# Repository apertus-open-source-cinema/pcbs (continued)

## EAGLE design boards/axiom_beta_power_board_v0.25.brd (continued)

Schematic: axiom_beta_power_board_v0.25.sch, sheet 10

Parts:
C49, C52, C55, C58, C61: 4u7; 0603-B
C50, C53, C56, C59, C62: DNP; 0402-B
C51, C54, C57, C60, C63: 10u; 0603-B
L9, L10, L11, L12, L13: L0805-A; 0805-A
MCN: MCP1727-ADJE/MF; DFN65P300X300X100-9N
MCS: MCP1727-ADJE/MF; DFN65P300X300X100-9N
MXN: MCP1727-ADJE/MF; DFN65P300X300X100-9N
MXS: MCP1727-ADJE/MF; DFN65P300X300X100-9N
R33, R35, R39, R41: RD; 0402-B
R34, R36, R40, R42: RC; 0402-B
R37: 102k; 0402-B
R38: 20k; 0402-B
R67, R68, R69, R70, R71, R72: R1206-B; 1206-B
R81: 2k0; 0402-B
R82: 1k6; 0402-B
R83: 2k7; 0402-B
R90: 15k; 0402-B
R91: 1k; 0402-B
U7: MCP23018-E/MJ; QFN50P400X400X80-25N
U14, U15, U22: PAC1720; DFN3X3_10LEAD
VIO: MCP1727-ADJE/MF; DFN65P300X300X100-9N

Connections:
BETA_5V: R70.1, U22.3 (SENSE2+); also elsewhere on the board
BETA_5V': C51.1, C54.1, C57.1, C60.1, C63.1, MCN.1 (VIN), MCN.2 (VIN), MCS.1 (VIN), MCS.2 (VIN), MXN.1 (VIN), MXN.2 (VIN), MXS.1 (VIN), MXS.2 (VIN), R70.2, U22.4 (SENSE2-), VIO.1 (VIN), VIO.2 (VIN); also elsewhere on the board
CSO_NE_V: R67.2, U14.2 (SENSE1-); also elsewhere on the board
CSO_N_V': L12.2, R67.1, U14.1 (SENSE1+)
CSO_SW_V: R71.2, U15.2 (SENSE1-); also elsewhere on the board
CSO_S_V': L10.2, R71.1, U15.1 (SENSE1+)
GND: C49.2, C50.2, C51.2, C52.2, C53.2, C54.2, C55.2, C56.2, C57.2, C58.2, C59.2, C60.2, C61.2, C62.2, C63.2, MCN.4 (GND), MCN.9 (EP), MCS.4 (GND), MCS.9 (EP), MXN.4 (GND), MXN.9 (EP), MXS.4 (GND), MXS.9 (EP), R34.2, R36.2, R38.2, R40.2, R42.2, R81.2, R82.2, R83.2, R91.2, U7.23 (VSS), U7.25 (VSS), U14.5 (GND), U14.EPAD (GND), U15.5 (GND), U15.EPAD (GND), U22.5 (GND), U22.EPAD (GND), VIO.4 (GND), VIO.9 (EP); also elsewhere on the board
MCN_EN: MCN.3 (!SHDN), U7.18 (GPA3)
MCN_PG: MCN.5 (PWRGD), U7.17 (GPA2)
MCS_EN: MCS.3 (!SHDN), U7.22 (GPA7)
MCS_PG: MCS.5 (PWRGD), U7.21 (GPA6)
MXN_EN: MXN.3 (!SHDN), U7.16 (GPA1)
MXN_PG: MXN.5 (PWRGD), U7.15 (GPA0)
MXS_EN: MXS.3 (!SHDN), U7.1 (GPB1)
MXS_PG: MXS.5 (PWRGD), U7.24 (GPB0)
unnamed: C49.1, L9.1, MXS.8 (VOUT), R41.1
unnamed: MXS.7 (ADJ), R41.2, R42.1
unnamed: C50.1, MXS.6 (CDELAY)
unnamed: R81.1, U14.6 (ASEL)
unnamed: R83.1, U15.6 (ASEL)
unnamed: C52.1, L10.1, MCS.8 (VOUT), R39.1
unnamed: MCS.7 (ADJ), R39.2, R40.1
unnamed: C53.1, MCS.6 (CDELAY)
unnamed: R82.1, U22.6 (ASEL)
unnamed: C55.1, L11.1, R37.1, VIO.8 (VOUT)
unnamed: R37.2, R38.1, VIO.7 (ADJ)
unnamed: C56.1, VIO.6 (CDELAY)
unnamed: C58.1, L12.1, MCN.8 (VOUT), R35.1
unnamed: MCN.7 (ADJ), R35.2, R36.1
unnamed: C59.1, MCN.6 (CDELAY)
unnamed: C61.1, L13.1, MXN.8 (VOUT), R33.1
unnamed: MXN.7 (ADJ), R33.2, R34.1
unnamed: C62.1, MXN.6 (CDELAY)
unnamed: R90.2, R91.1, U7.11 (ADDR)
PCIE_N_V: R68.2, U14.4 (SENSE2-); also elsewhere on the board
PCIE_N_V': L13.2, R68.1, U14.3 (SENSE2+)
PCIE_S_V: R72.2, U15.4 (SENSE2-); also elsewhere on the board
PCIE_S_V': L9.2, R72.1, U15.3 (SENSE2+)
PMOD_SCL: U7.9 (SCL), U14.9 (SMCLK), U15.9 (SMCLK), U22.9 (SMCLK); also elsewhere on the board
PMOD_SDA: U7.10 (SDA), U14.8 (SMDATA), U15.8 (SMDATA), U22.8 (SMDATA); also elsewhere on the board
VCC: R90.1, U7.8 (VDD), U7.12 (!RESET), U14.10 (VDD), U15.10 (VDD), U22.10 (VDD); also elsewhere on the board
VCCIO: L11.2; also elsewhere on the board
VIO_EN: U7.20 (GPA5), VIO.3 (!SHDN)
VIO_PG: U7.19 (GPA4), VIO.5 (PWRGD)
ZED_5V: R69.1, U22.1 (SENSE1+); also elsewhere on the board
ZED_5V': R69.2, U22.2 (SENSE1-); also elsewhere on the board

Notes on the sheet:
AXIOM Beta Test
Copyright (C) 2015 H.Poetzl Licensed under CERN OHL v.1.2
Power, Control and Sensing
[ID=0x20]
[0x29]
[0x28]
[0x2A]

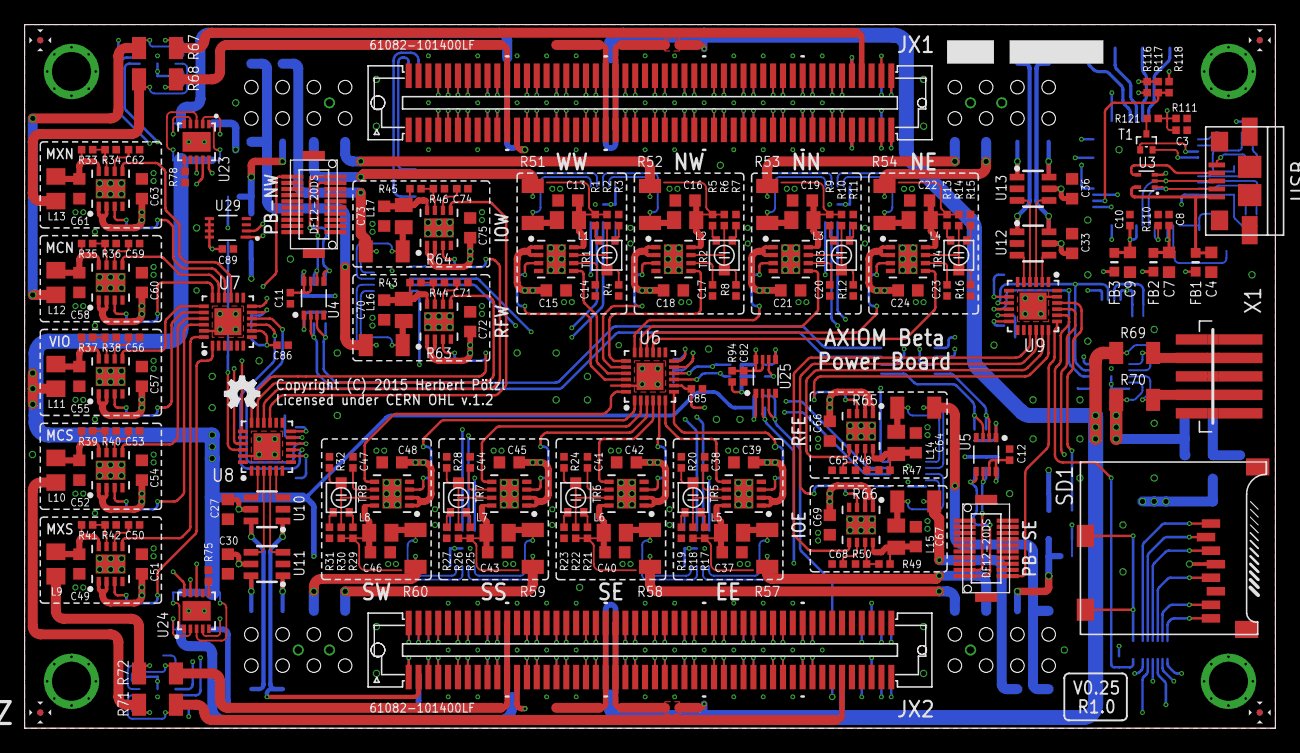
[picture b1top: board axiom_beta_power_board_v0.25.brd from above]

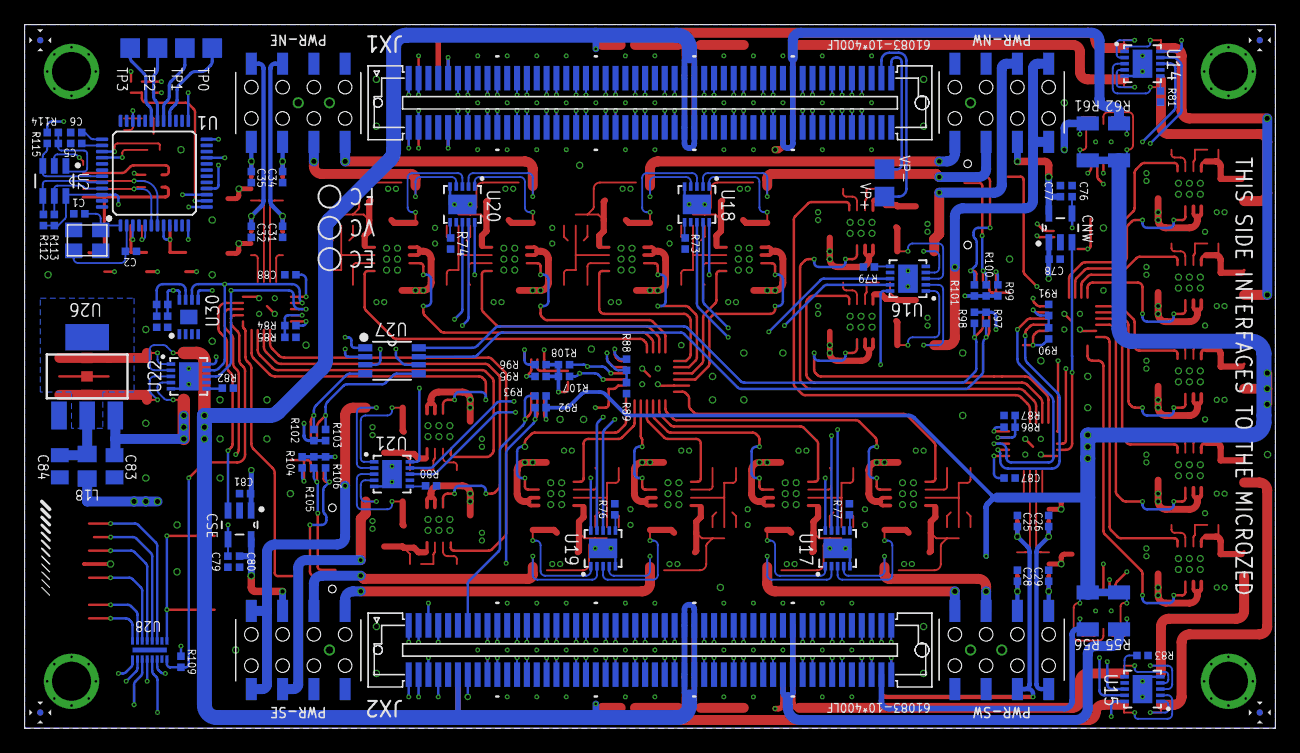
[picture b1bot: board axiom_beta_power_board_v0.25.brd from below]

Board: 4 copper layers, 101.6 x 57.1 mm, 309 parts (97 on the bottom side), 366 nets.

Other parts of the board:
LOGO1: OSHW_LOGO_FILLX0100-NT; OSHW_FILLX100_NOTEXT

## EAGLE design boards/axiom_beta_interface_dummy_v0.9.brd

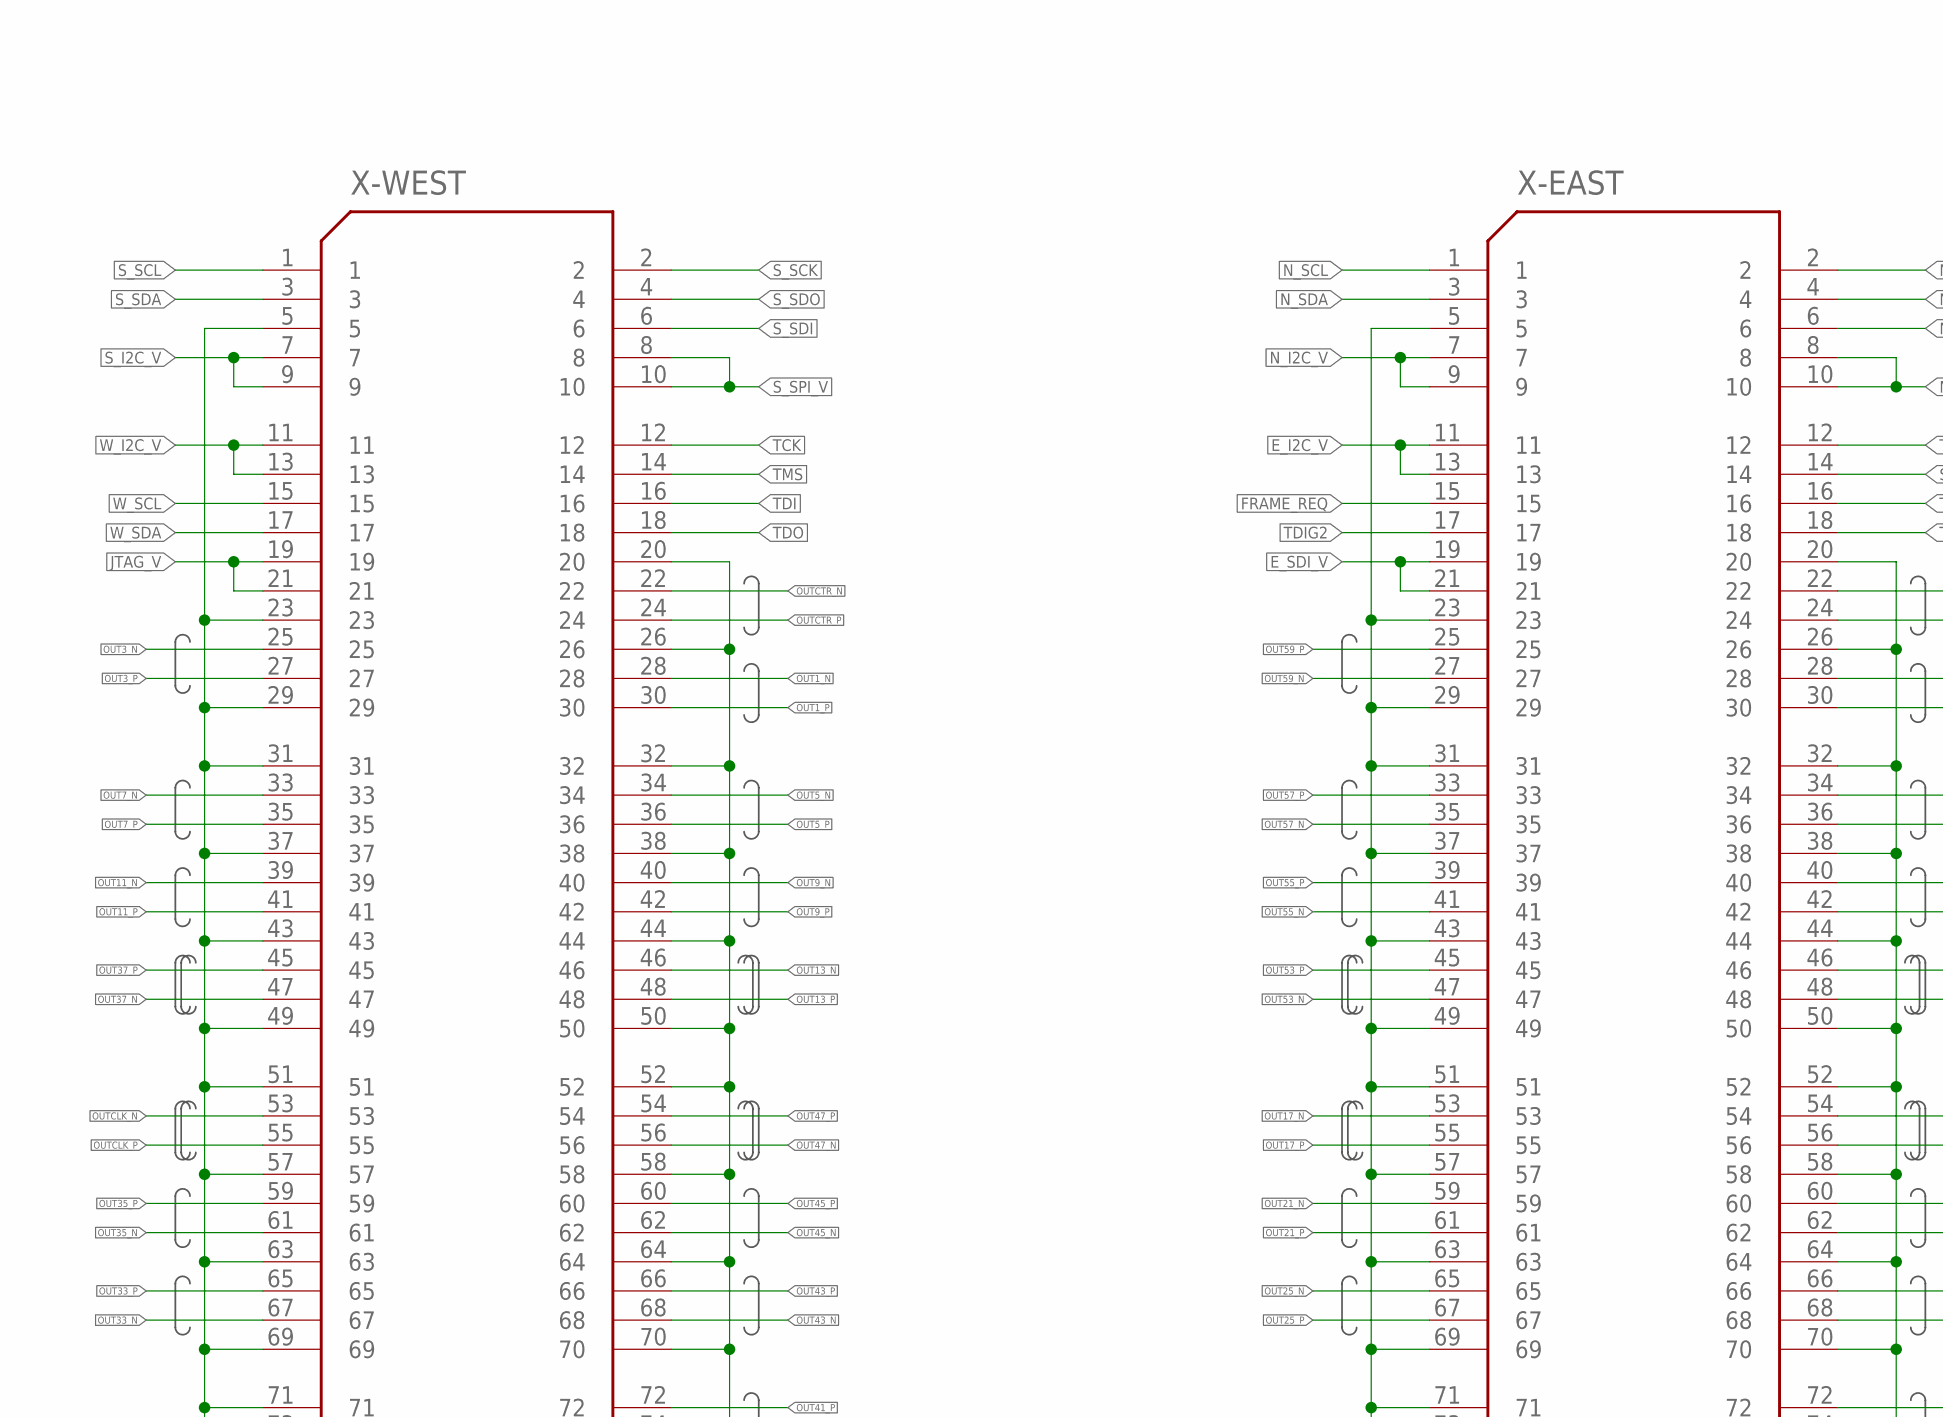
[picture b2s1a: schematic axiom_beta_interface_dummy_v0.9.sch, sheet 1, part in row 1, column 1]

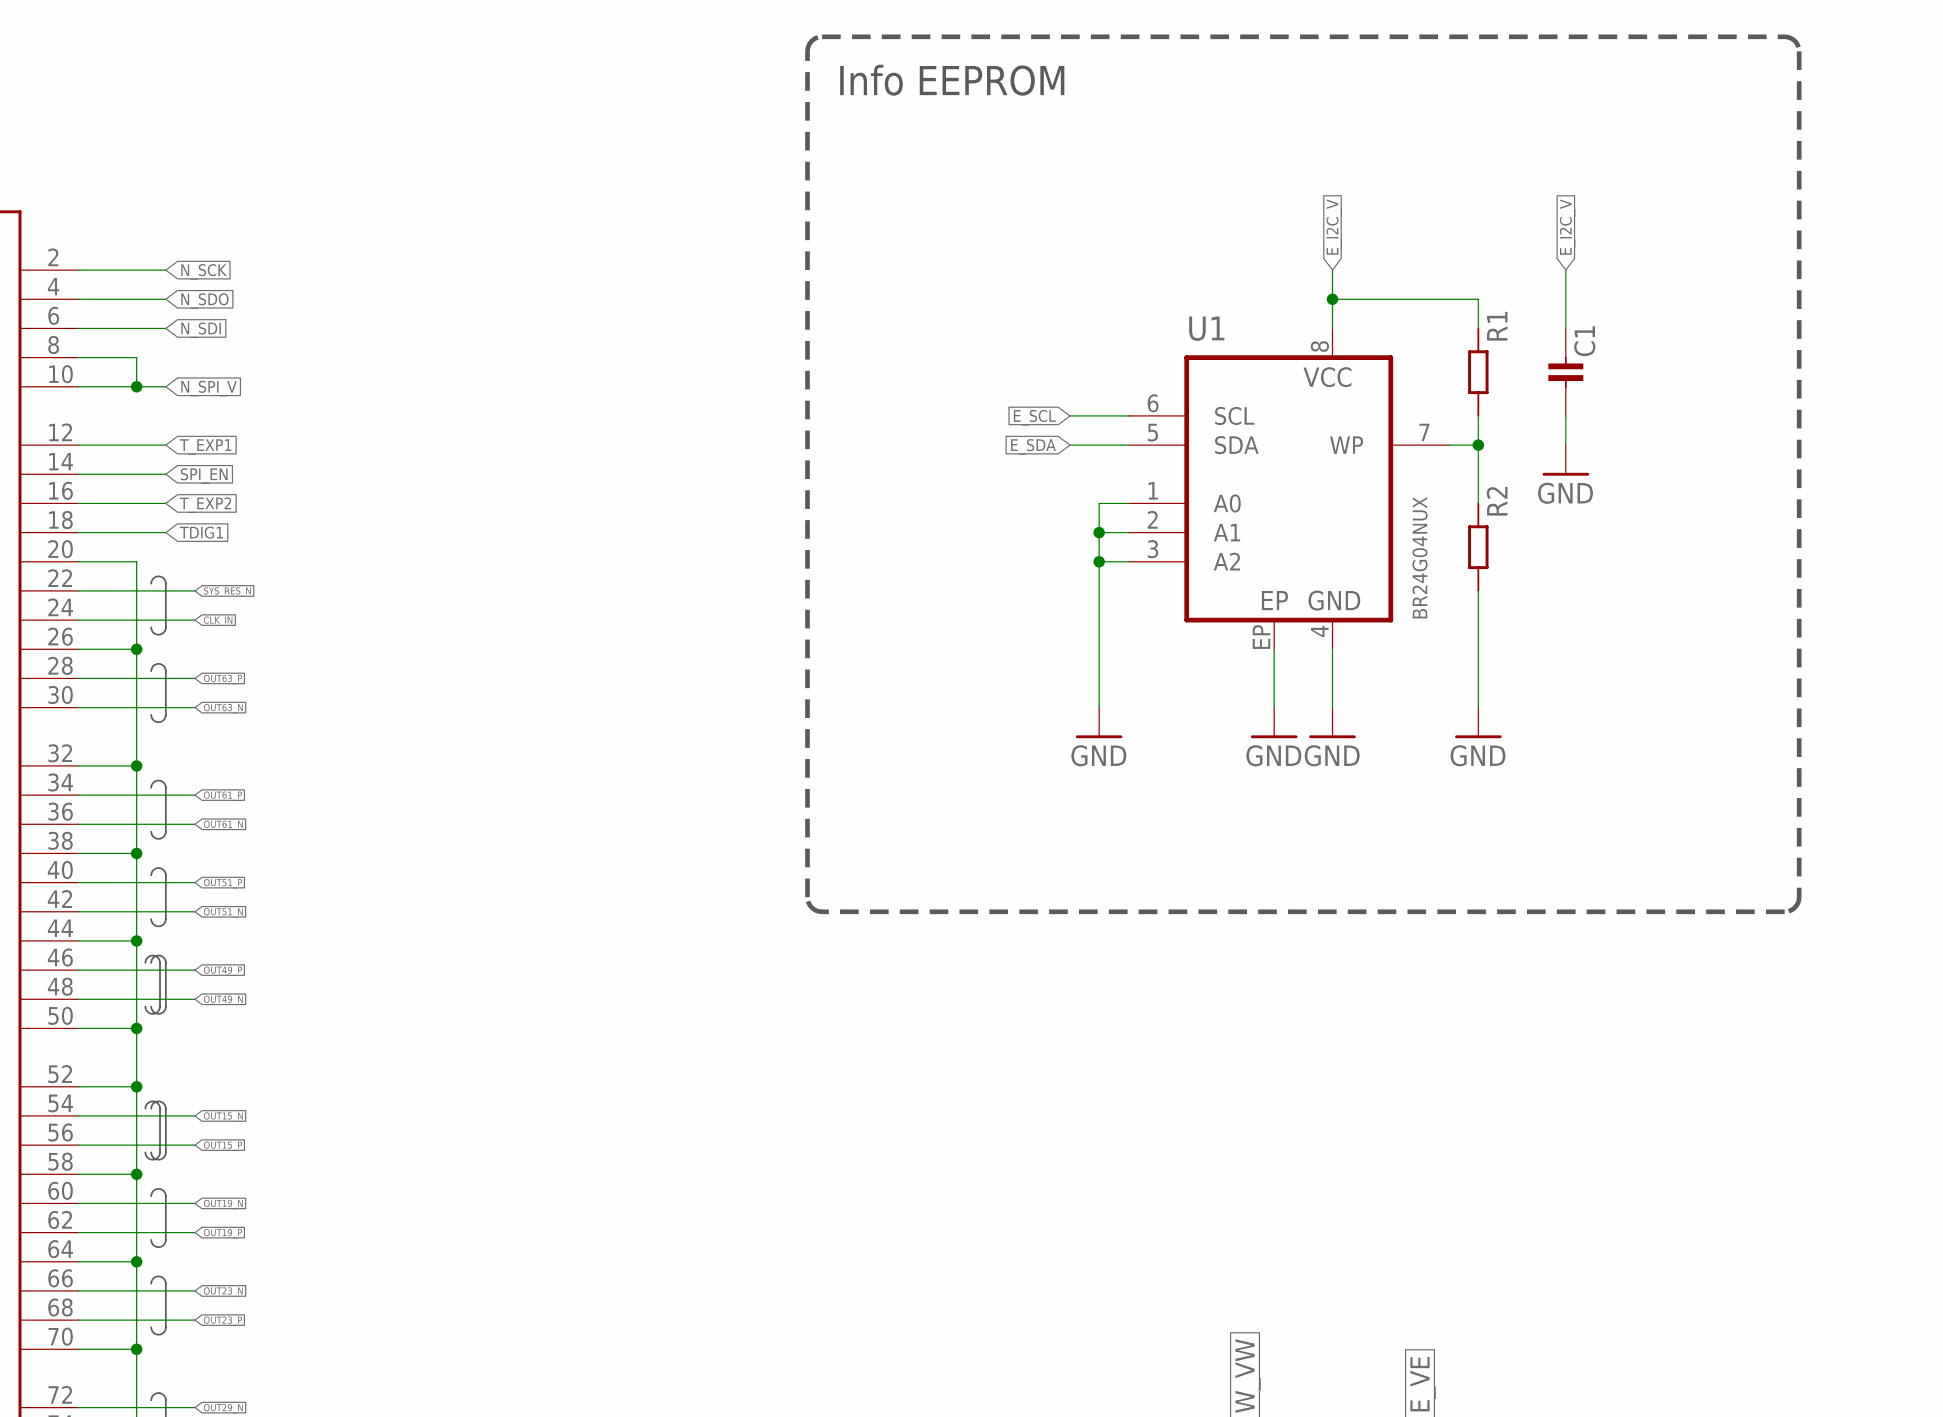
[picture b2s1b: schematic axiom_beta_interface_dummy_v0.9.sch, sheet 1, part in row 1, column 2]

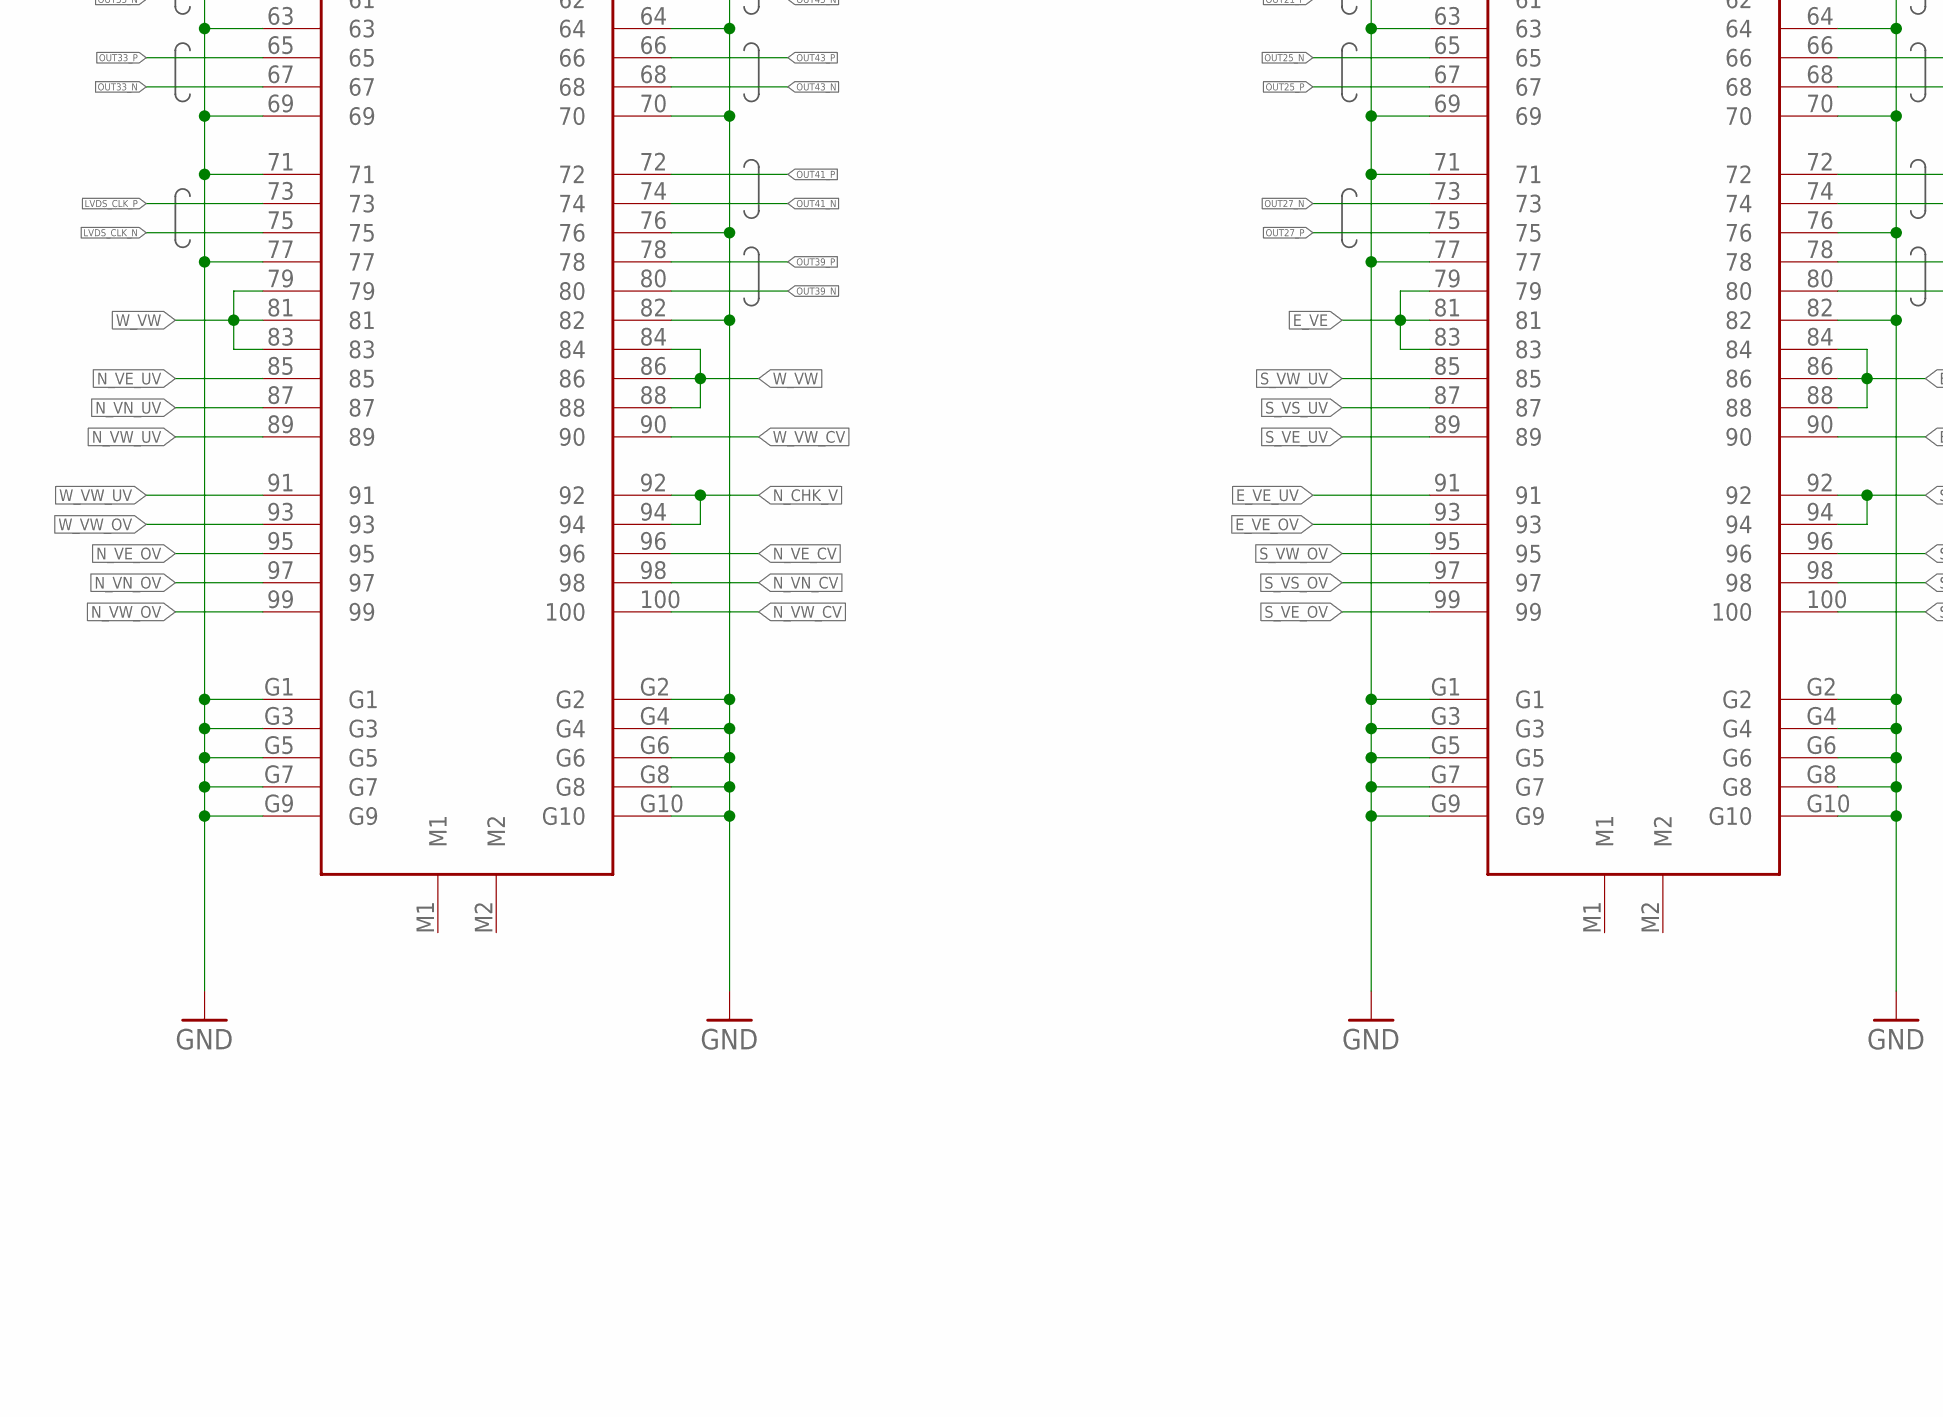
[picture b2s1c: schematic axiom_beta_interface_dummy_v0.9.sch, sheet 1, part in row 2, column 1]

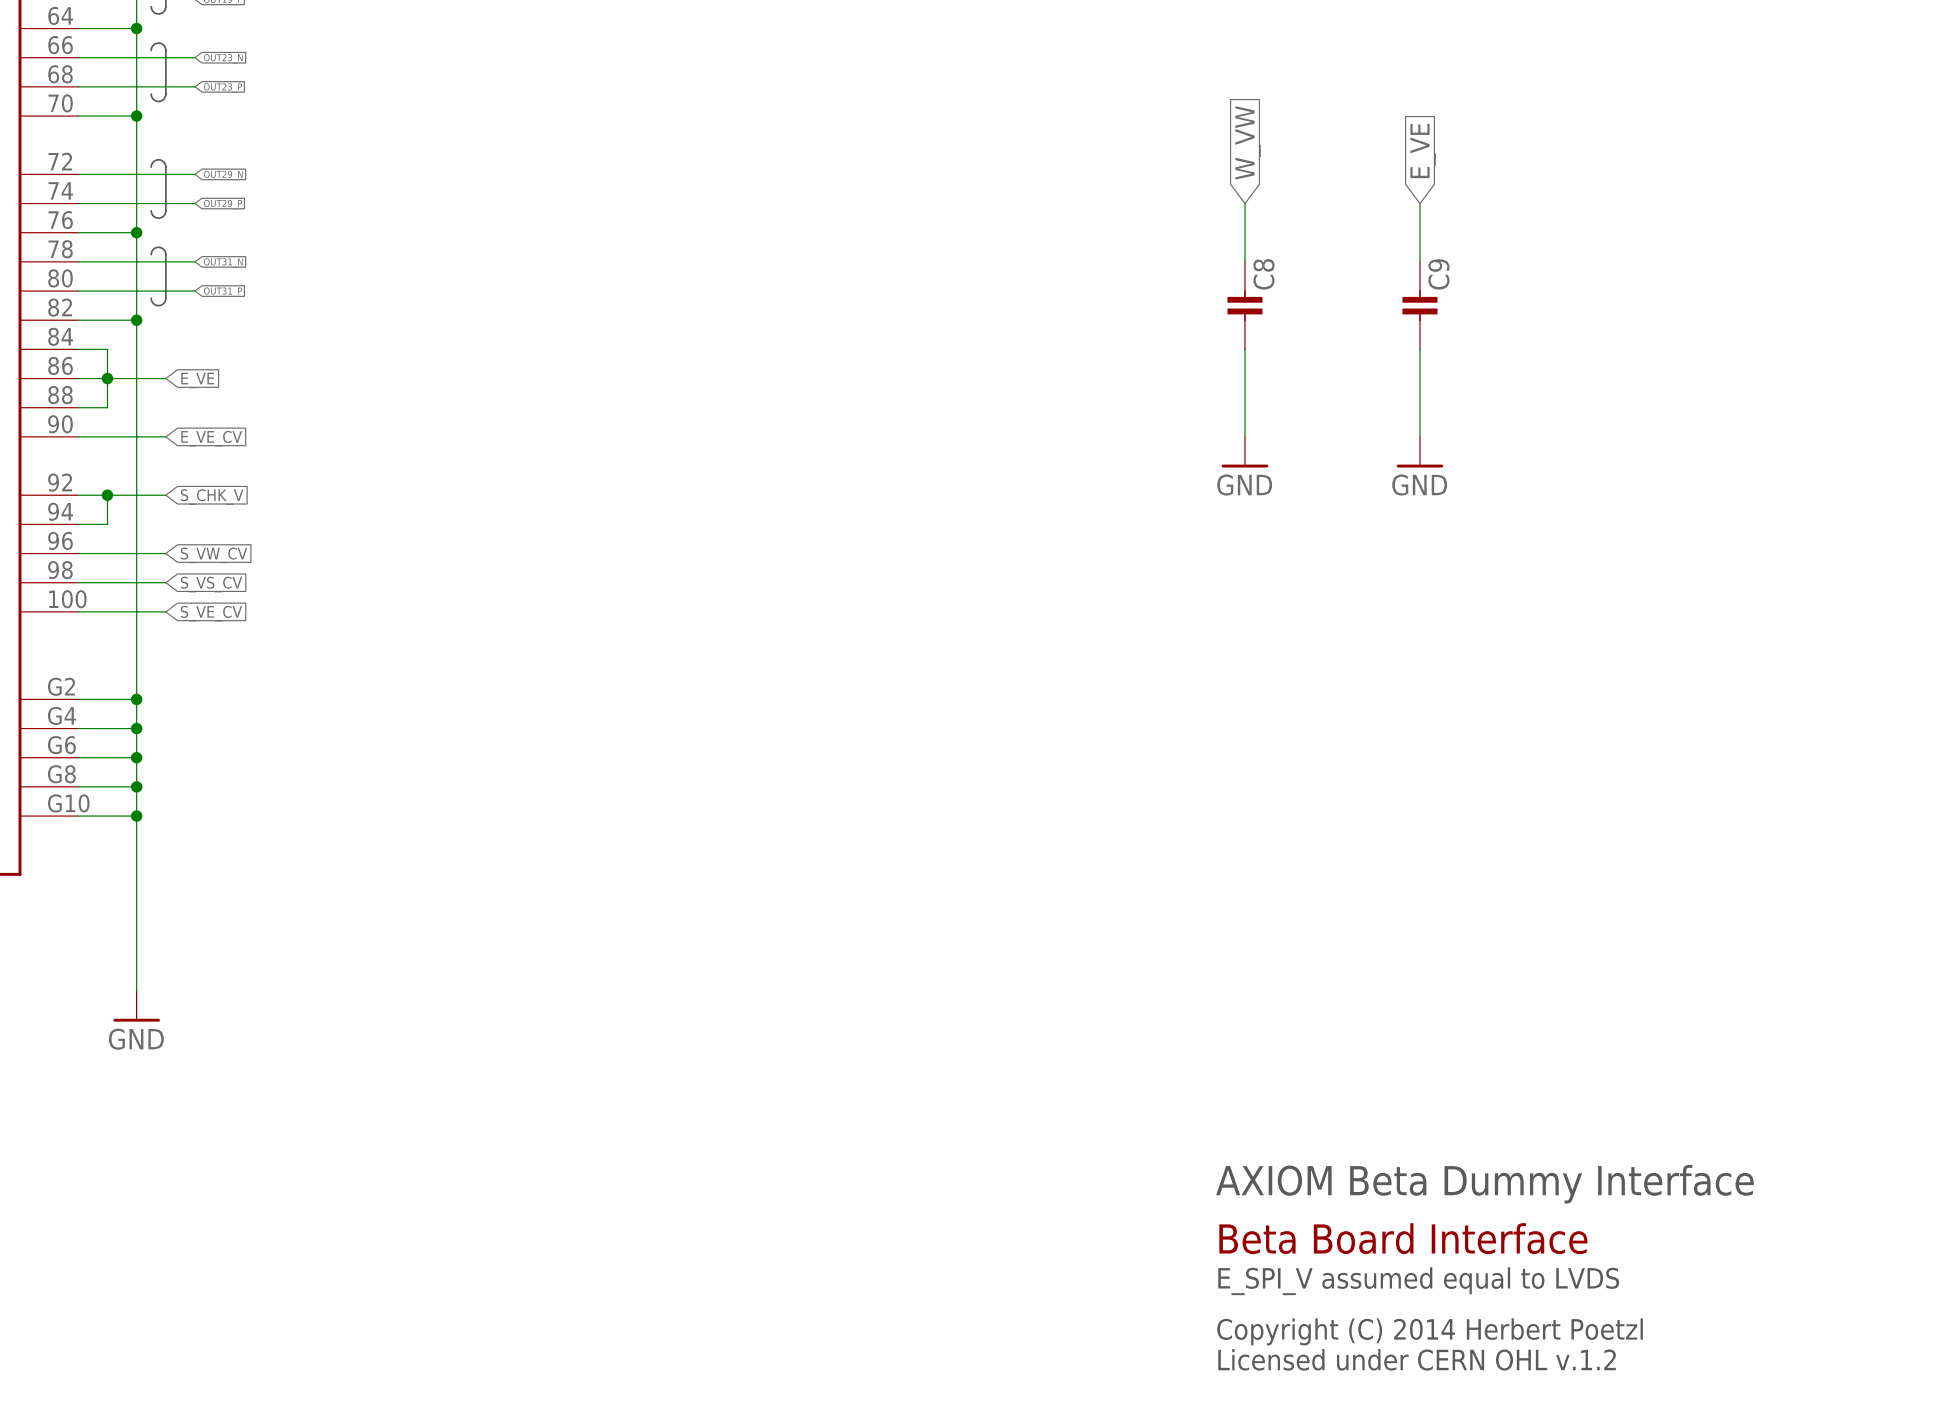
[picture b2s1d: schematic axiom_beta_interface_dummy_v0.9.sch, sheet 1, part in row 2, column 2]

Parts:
C1: C0402-B; 0402-B
C8, C9: C0805-B; 0805-B
R1, R2: R0402-B; 0402-B
U1: BR24G04NUX; DFN200X300X100-9N
X-EAST: FX10-100/10P; FX10A-100P/10
X-WEST: FX10-100/10P; FX10A-100P/10

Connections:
CLK_IN: X-EAST.24; also elsewhere on the board
E_I2C_V: C1.1, R1.1, U1.8 (VCC), X-EAST.11, X-EAST.13
E_SCL: U1.6 (SCL)
E_SDA: U1.5 (SDA)
E_SDI_V: X-EAST.19, X-EAST.21
E_VE: C9.1, X-EAST.79, X-EAST.81, X-EAST.83, X-EAST.84, X-EAST.86, X-EAST.88; also elsewhere on the board
E_VE_CV: X-EAST.90
E_VE_OV: X-EAST.93
E_VE_UV: X-EAST.91
FRAME_REQ: X-EAST.15; also elsewhere on the board
GND: C1.2, C8.2, C9.2, R2.2, U1.1 (A0), U1.2 (A1), U1.3 (A2), U1.4 (GND), U1.EP, X-EAST.5, X-EAST.20, X-EAST.23, X-EAST.26, X-EAST.29, X-EAST.31, X-EAST.32, X-EAST.37, X-EAST.38, X-EAST.43, X-EAST.44, X-EAST.49, X-EAST.50, X-EAST.51, X-EAST.52, X-EAST.57, X-EAST.58, X-EAST.63, X-EAST.64, X-EAST.69, X-EAST.70, X-EAST.71, X-EAST.76, X-EAST.77, X-EAST.82, X-EAST.G1, X-EAST.G2, X-EAST.G3, X-EAST.G4, X-EAST.G5, X-EAST.G6, X-EAST.G7, X-EAST.G8, X-EAST.G9, X-EAST.G10, X-WEST.5, X-WEST.20, X-WEST.23, X-WEST.26, X-WEST.29, X-WEST.31, X-WEST.32, X-WEST.37, X-WEST.38, X-WEST.43, X-WEST.44, X-WEST.49, X-WEST.50, X-WEST.51, X-WEST.52, X-WEST.57, X-WEST.58, X-WEST.63, X-WEST.64, X-WEST.69, X-WEST.70, X-WEST.71, X-WEST.76, X-WEST.77, X-WEST.82, X-WEST.G1, X-WEST.G2, X-WEST.G3, X-WEST.G4, X-WEST.G5, X-WEST.G6, X-WEST.G7, X-WEST.G8, X-WEST.G9, X-WEST.G10; also elsewhere on the board
JTAG_V: X-WEST.19, X-WEST.21
LVDS_CLK_N: X-WEST.75; also elsewhere on the board
LVDS_CLK_P: X-WEST.73; also elsewhere on the board
unnamed: R1.2, R2.1, U1.7 (WP)
N_CHK_V: X-WEST.92, X-WEST.94; also elsewhere on the board
N_I2C_V: X-EAST.7, X-EAST.9; also elsewhere on the board
N_SCK: X-EAST.2; also elsewhere on the board
N_SCL: X-EAST.1; also elsewhere on the board
N_SDA: X-EAST.3; also elsewhere on the board
N_SDI: X-EAST.6; also elsewhere on the board
N_SDO: X-EAST.4; also elsewhere on the board
N_SPI_V: X-EAST.8, X-EAST.10; also elsewhere on the board
N_VE_CV: X-WEST.96; also elsewhere on the board
N_VE_OV: X-WEST.95; also elsewhere on the board
N_VE_UV: X-WEST.85; also elsewhere on the board
N_VN_CV: X-WEST.98; also elsewhere on the board
N_VN_OV: X-WEST.97; also elsewhere on the board
N_VN_UV: X-WEST.87; also elsewhere on the board
N_VW_CV: X-WEST.100; also elsewhere on the board
N_VW_OV: X-WEST.99; also elsewhere on the board
N_VW_UV: X-WEST.89; also elsewhere on the board
OUT1_N: X-WEST.28; also elsewhere on the board
OUT1_P: X-WEST.30; also elsewhere on the board
OUT3_N: X-WEST.25; also elsewhere on the board
OUT3_P: X-WEST.27; also elsewhere on the board
OUT5_N: X-WEST.34; also elsewhere on the board
OUT5_P: X-WEST.36; also elsewhere on the board
OUT7_N: X-WEST.33; also elsewhere on the board
OUT7_P: X-WEST.35; also elsewhere on the board
OUT9_N: X-WEST.40; also elsewhere on the board
OUT9_P: X-WEST.42; also elsewhere on the board
OUT11_N: X-WEST.39; also elsewhere on the board
OUT11_P: X-WEST.41; also elsewhere on the board
OUT13_N: X-WEST.46; also elsewhere on the board
OUT13_P: X-WEST.48; also elsewhere on the board
OUT15_N: X-EAST.54; also elsewhere on the board
OUT15_P: X-EAST.56; also elsewhere on the board
OUT17_N: X-EAST.53; also elsewhere on the board
OUT17_P: X-EAST.55; also elsewhere on the board
OUT19_N: X-EAST.60; also elsewhere on the board
OUT19_P: X-EAST.62; also elsewhere on the board
OUT21_N: X-EAST.59; also elsewhere on the board
OUT21_P: X-EAST.61; also elsewhere on the board
OUT23_N: X-EAST.66; also elsewhere on the board
OUT23_P: X-EAST.68; also elsewhere on the board
OUT25_N: X-EAST.65; also elsewhere on the board
OUT25_P: X-EAST.67; also elsewhere on the board
OUT27_N: X-EAST.73; also elsewhere on the board
OUT27_P: X-EAST.75; also elsewhere on the board
OUT29_N: X-EAST.72; also elsewhere on the board
OUT29_P: X-EAST.74; also elsewhere on the board
OUT31_N: X-EAST.78; also elsewhere on the board
OUT31_P: X-EAST.80; also elsewhere on the board
OUT33_N: X-WEST.67; also elsewhere on the board
OUT33_P: X-WEST.65; also elsewhere on the board
OUT35_N: X-WEST.61; also elsewhere on the board
OUT35_P: X-WEST.59; also elsewhere on the board
OUT37_N: X-WEST.47; also elsewhere on the board
OUT37_P: X-WEST.45; also elsewhere on the board
OUT39_N: X-WEST.80; also elsewhere on the board
OUT39_P: X-WEST.78; also elsewhere on the board
OUT41_N: X-WEST.74; also elsewhere on the board
OUT41_P: X-WEST.72; also elsewhere on the board
OUT43_N: X-WEST.68; also elsewhere on the board
OUT43_P: X-WEST.66; also elsewhere on the board
OUT45_N: X-WEST.62; also elsewhere on the board
OUT45_P: X-WEST.60; also elsewhere on the board
OUT47_N: X-WEST.56; also elsewhere on the board
OUT47_P: X-WEST.54; also elsewhere on the board
OUT49_N: X-EAST.48; also elsewhere on the board
OUT49_P: X-EAST.46; also elsewhere on the board
OUT51_N: X-EAST.42; also elsewhere on the board
OUT51_P: X-EAST.40; also elsewhere on the board
OUT53_N: X-EAST.47; also elsewhere on the board
OUT53_P: X-EAST.45; also elsewhere on the board
OUT55_N: X-EAST.41; also elsewhere on the board
OUT55_P: X-EAST.39; also elsewhere on the board
OUT57_N: X-EAST.35; also elsewhere on the board
OUT57_P: X-EAST.33; also elsewhere on the board
OUT59_N: X-EAST.27; also elsewhere on the board
OUT59_P: X-EAST.25; also elsewhere on the board
OUT61_N: X-EAST.36; also elsewhere on the board
OUT61_P: X-EAST.34; also elsewhere on the board
OUT63_N: X-EAST.30; also elsewhere on the board
OUT63_P: X-EAST.28; also elsewhere on the board
OUTCLK_N: X-WEST.53; also elsewhere on the board
OUTCLK_P: X-WEST.55; also elsewhere on the board
OUTCTR_N: X-WEST.22; also elsewhere on the board
OUTCTR_P: X-WEST.24; also elsewhere on the board
SPI_EN: X-EAST.14; also elsewhere on the board
SYS_RES_N: X-EAST.22; also elsewhere on the board
S_CHK_V: X-EAST.92, X-EAST.94; also elsewhere on the board
S_I2C_V: X-WEST.7, X-WEST.9; also elsewhere on the board
S_SCK: X-WEST.2; also elsewhere on the board
S_SCL: X-WEST.1; also elsewhere on the board
S_SDA: X-WEST.3; also elsewhere on the board
S_SDI: X-WEST.6; also elsewhere on the board
S_SDO: X-WEST.4; also elsewhere on the board
S_SPI_V: X-WEST.8, X-WEST.10; also elsewhere on the board
S_VE_CV: X-EAST.100; also elsewhere on the board
S_VE_OV: X-EAST.99; also elsewhere on the board
S_VE_UV: X-EAST.89; also elsewhere on the board
S_VS_CV: X-EAST.98; also elsewhere on the board
S_VS_OV: X-EAST.97; also elsewhere on the board
S_VS_UV: X-EAST.87; also elsewhere on the board
S_VW_CV: X-EAST.96; also elsewhere on the board
S_VW_OV: X-EAST.95; also elsewhere on the board
S_VW_UV: X-EAST.85; also elsewhere on the board
TCK: X-WEST.12
TDI: X-WEST.16
TDIG1: X-EAST.18; also elsewhere on the board
TDIG2: X-EAST.17; also elsewhere on the board
TDO: X-WEST.18
TMS: X-WEST.14
T_EXP1: X-EAST.12; also elsewhere on the board
T_EXP2: X-EAST.16; also elsewhere on the board
W_I2C_V: X-WEST.11, X-WEST.13
W_SCL: X-WEST.15
W_SDA: X-WEST.17
W_VW: C8.1, X-WEST.79, X-WEST.81, X-WEST.83, X-WEST.84, X-WEST.86, X-WEST.88; also elsewhere on the board
W_VW_CV: X-WEST.90
W_VW_OV: X-WEST.93
W_VW_UV: X-WEST.91

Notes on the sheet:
Info EEPROM
AXIOM Beta Dummy Interface
Copyright (C) 2014 Herbert Poetzl Licensed under CERN OHL v.1.2
Beta Board Interface
E_SPI_V assumed equal to LVDS
